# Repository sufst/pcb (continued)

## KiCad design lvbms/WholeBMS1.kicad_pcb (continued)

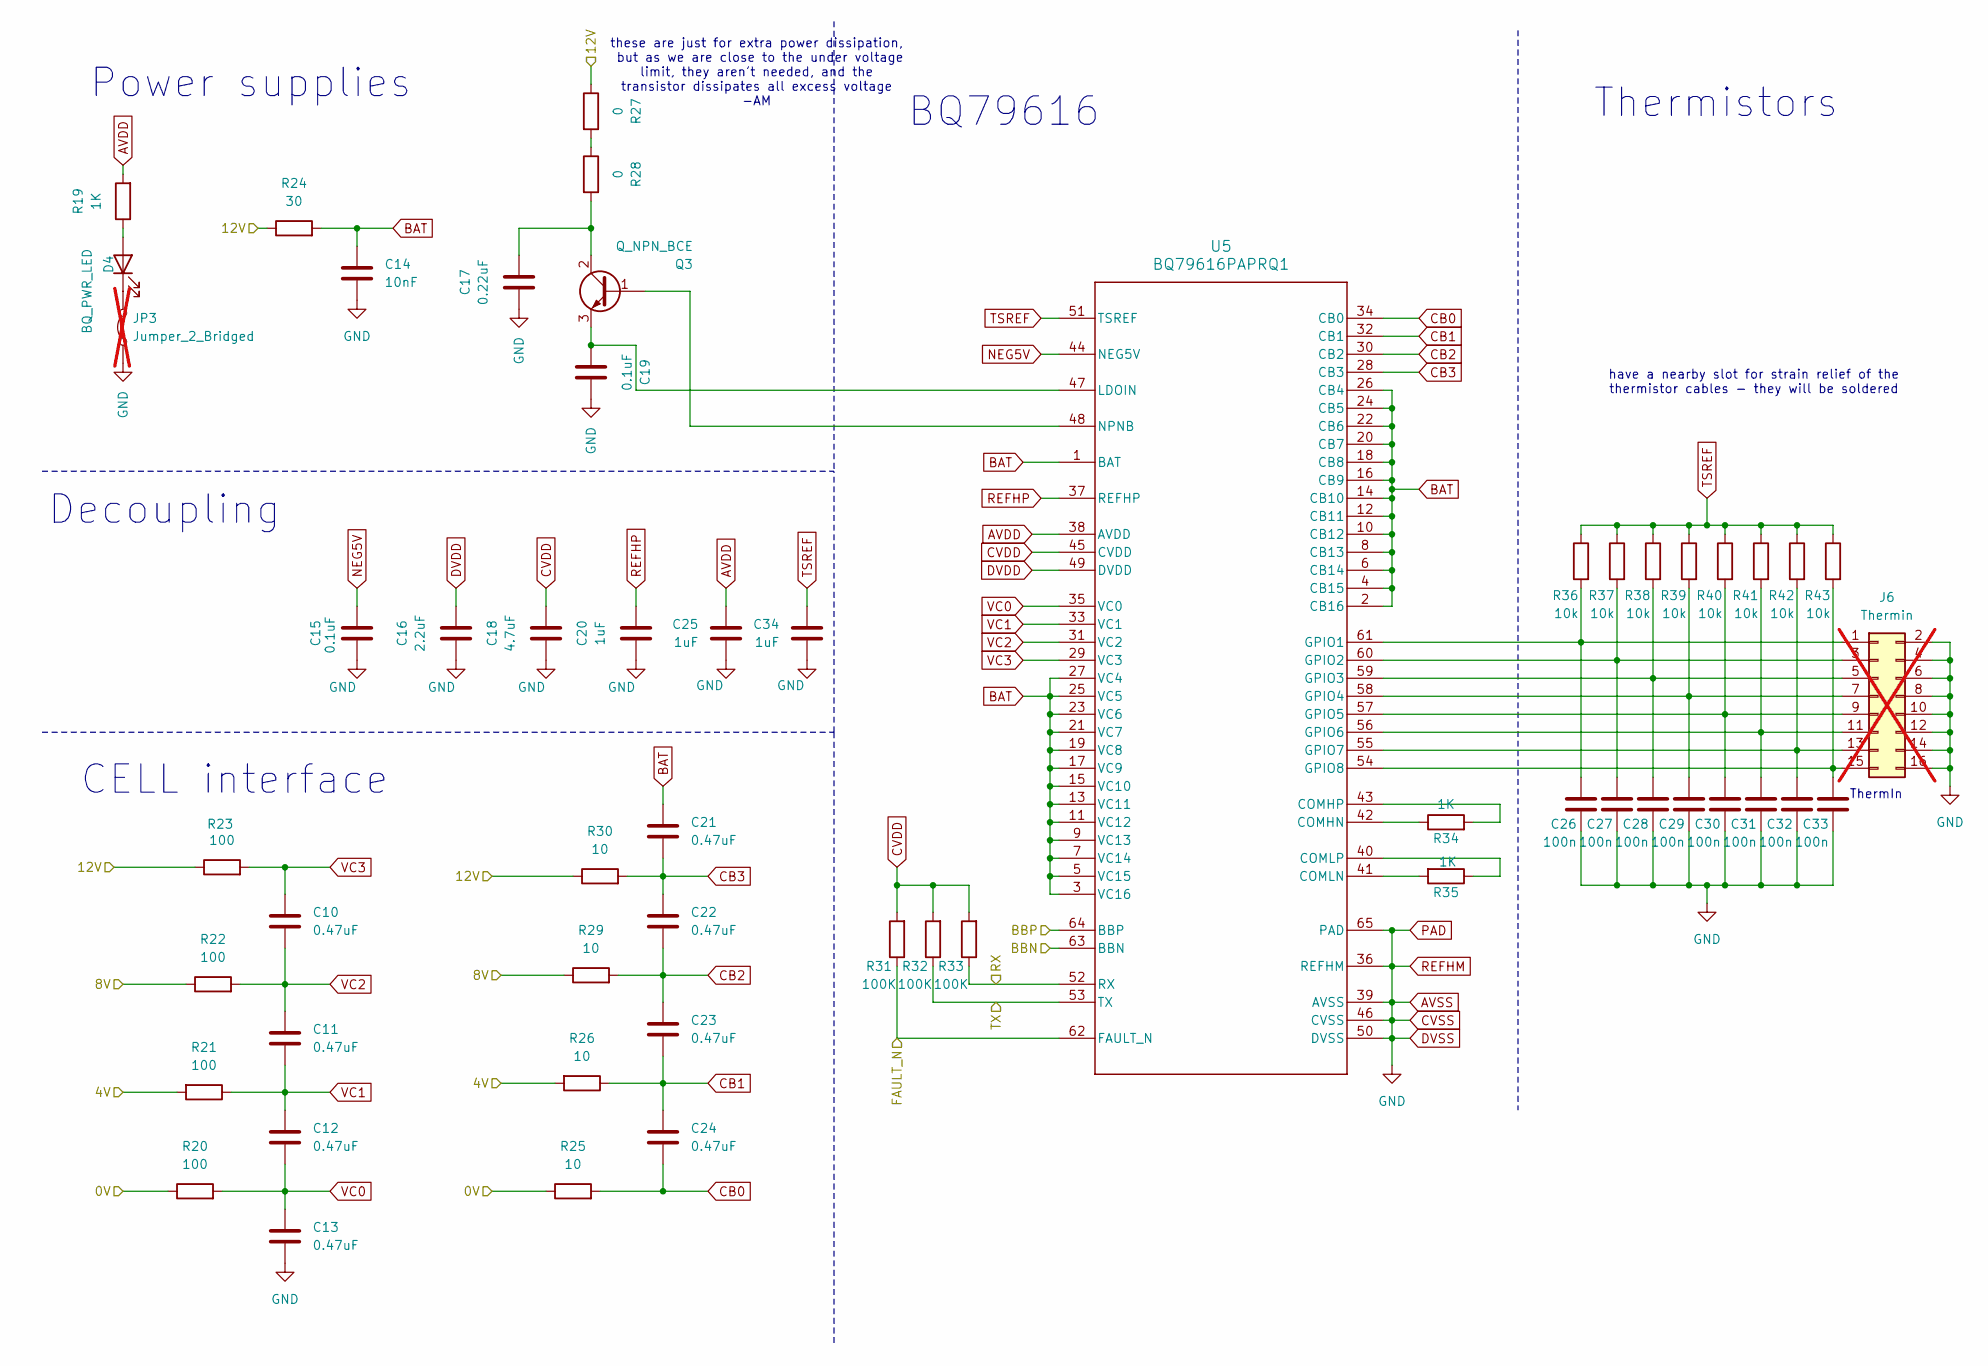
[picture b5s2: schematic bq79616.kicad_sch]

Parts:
C10, C11, C12, C13, C21, C22, C23, C24: 0.47uF; C_0603_1608Metric
C14: 10nF; C_0603_1608Metric
C15, C19: 0.1uF; C_0603_1608Metric
C16: 2.2uF; C_0603_1608Metric
C17: 0.22uF; C_0603_1608Metric
C18: 4.7uF; C_0603_1608Metric
C20, C25, C34: 1uF; C_0603_1608Metric
C26, C27, C28, C29, C30, C31, C32, C33: 100n; C_0603_1608Metric
D4: BQ_PWR_LED; LED_0805_2012Metric_Pad1.15x1.40mm_HandSolder
J6: Thermin; PinSocket_2x08_P2.54mm_Vertical; not fitted
JP3: Jumper_2_Bridged; SolderJumper-2_P1.3mm_Bridged_RoundedPad1.0x1.5mm; not fitted
Q3: Q_NPN_BCE; TO-252-3_TabPin2
R19, R34, R35: 1K; R_0603_1608Metric
R20, R21, R22, R23: 100; R_0603_1608Metric
R24: 30; R_0603_1608Metric
R25, R26, R29, R30: 10; R_2512_6332Metric
R27, R28: 0; R_0603_1608Metric
R31, R32, R33: 100K; R_0603_1608Metric
R36, R37, R38, R39, R40, R41, R42, R43: 10k; R_0603_1608Metric
U5: BQ79616PAPRQ1; PAP0064F-IPC_A

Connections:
/Bat1In: R21.2, R26.2; also elsewhere on the board
/Bat2In: R22.1, R29.1; also elsewhere on the board
/Bat3InFuse: U5.63 (BBN); also elsewhere on the board
/Bat3In_Sh: R23.1, R24.1, R27.1, R30.1, U5.64 (BBP); also elsewhere on the board
/FAULT_N: R31.1, U5.62 (FAULT_N); also elsewhere on the board
/MCU_RX: R32.1, U5.53 (TX); also elsewhere on the board
/MCU_TX: R33.1, U5.52 (RX); also elsewhere on the board
AVDD: C25.1, R19.2, U5.38 (AVDD)
AVSS: C13.2, C14.2, C15.2, C16.2, C17.1, C18.2, C19.1, C20.2, C25.2, C26.2, C27.2, C28.2, C29.2, C30.2, C31.2, C32.2, C33.2, C34.2, J6.2, J6.4, J6.6, J6.8, J6.10, J6.12, J6.14, J6.16, JP3.1 (A), R20.1, R25.1, U5.36 (REFHM), U5.39 (AVSS), U5.46 (CVSS), U5.50 (DVSS), U5.65 (PAD); also elsewhere on the board
BAT: C14.1, C21.1, R24.2, U5.1 (BAT), U5.2 (CB16), U5.3 (VC16), U5.4 (CB15), U5.5 (VC15), U5.6 (CB14), U5.7 (VC14), U5.8 (CB13), U5.9 (VC13), U5.10 (CB12), U5.11 (VC12), U5.12 (CB11), U5.13 (VC11), U5.14 (CB10), U5.15 (VC10), U5.16 (CB9), U5.17 (VC9), U5.18 (CB8), U5.19 (VC8), U5.20 (CB7), U5.21 (VC7), U5.22 (CB6), U5.23 (VC6), U5.24 (CB5), U5.25 (VC5), U5.26 (CB4), U5.27 (VC4)
CB0: C24.1, R25.2, U5.34 (CB0)
CB1: C23.2, C24.2, R26.1, U5.32 (CB1)
CB2: C22.2, C23.1, R29.2, U5.30 (CB2)
CB3: C21.2, C22.1, R30.2, U5.28 (CB3)
CVDD: C18.1, R31.2, R32.2, R33.2, U5.45 (CVDD)
DVDD: C16.1, U5.49 (DVDD)
NEG5V: C15.1, U5.44 (NEG5V)
unnamed: D4.2 (A), R19.1
unnamed: D4.1 (K), JP3.2 (B)
unnamed: C26.1, J6.1, R36.2, U5.61 (GPIO1)
unnamed: C27.1, J6.3, R37.2, U5.60 (GPIO2)
unnamed: C28.1, J6.5, R38.2, U5.59 (GPIO3)
unnamed: C29.1, J6.7, R39.2, U5.58 (GPIO4)
unnamed: C30.1, J6.9, R40.2, U5.57 (GPIO5)
unnamed: C31.1, J6.11, R41.2, U5.56 (GPIO6)
unnamed: C32.1, J6.13, R42.2, U5.55 (GPIO7)
unnamed: C33.1, J6.15, R43.2, U5.54 (GPIO8)
unnamed: Q3.1 (B), U5.48 (NPNB)
unnamed: C17.2, Q3.2 (C), R28.2
unnamed: C19.2, Q3.3 (E), U5.47 (LDOIN)
unnamed: R27.2, R28.1
unnamed: R34.1, U5.42 (COMHN)
unnamed: R34.2, U5.43 (COMHP)
unnamed: R35.2, U5.41 (COMLN)
unnamed: R35.1, U5.40 (COMLP)
REFHP: C20.1, U5.37 (REFHP)
TSREF: C34.1, R36.1, R37.1, R38.1, R39.1, R40.1, R41.1, R42.1, R43.1, U5.51 (TSREF)
VC0: C12.1, C13.1, R20.2, U5.35 (VC0)
VC1: C11.2, C12.2, R21.1, U5.33 (VC1)
VC2: C10.2, C11.1, R22.2, U5.31 (VC2)
VC3: C10.1, R23.2, U5.29 (VC3)

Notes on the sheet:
Thermistors
these are just for extra power dissipation, but as we are close to the under voltage limit, they aren't needed, and the transistor dissipates all excess voltage -AM
CELL interface
Power supplies
have a nearby slot for strain relief of the thermistor cables - they will be soldered
Decoupling
BQ79616
ThermIn

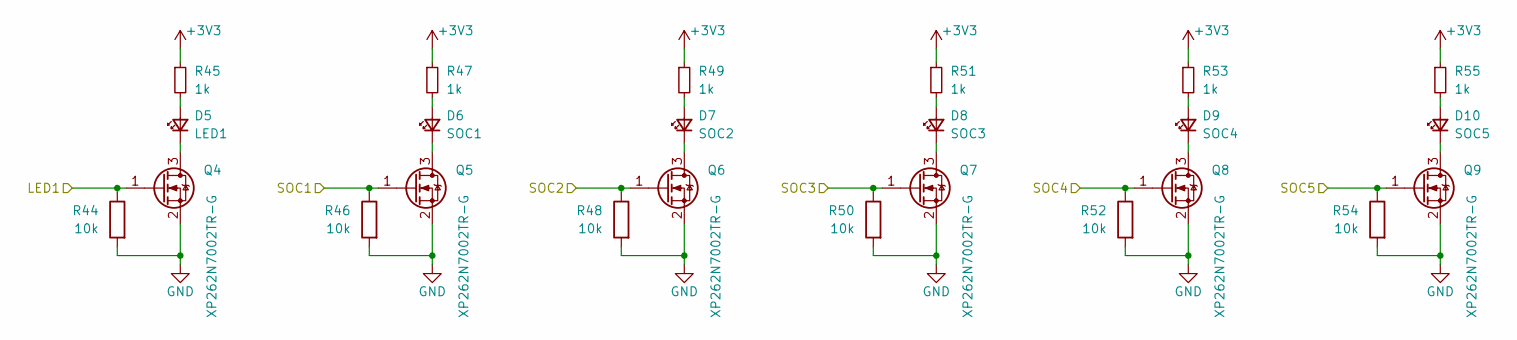
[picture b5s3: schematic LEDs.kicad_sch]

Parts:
D5: LED1; LED_0805_2012Metric_Pad1.15x1.40mm_HandSolder
D6: SOC1; LED_0805_2012Metric_Pad1.15x1.40mm_HandSolder
D7: SOC2; LED_0805_2012Metric_Pad1.15x1.40mm_HandSolder
D8: SOC3; LED_0805_2012Metric_Pad1.15x1.40mm_HandSolder
D9: SOC4; LED_0805_2012Metric_Pad1.15x1.40mm_HandSolder
D10: SOC5; LED_0805_2012Metric_Pad1.15x1.40mm_HandSolder
Q4, Q5, Q6, Q7, Q8, Q9: XP262N7002TR-G; SOT-23
R44, R46, R48, R50, R52, R54: 10k; R_0603_1608Metric
R45, R47, R49, R51, R53, R55: 1k; R_0603_1608Metric

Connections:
+3V3: R45.1, R47.1, R49.1, R51.1, R53.1, R55.1; also elsewhere on the board
/LED1: Q4.1 (G), R44.1; also elsewhere on the board
/SOC1: Q5.1 (G), R46.1; also elsewhere on the board
/SOC2: Q6.1 (G), R48.1; also elsewhere on the board
/SOC3: Q7.1 (G), R50.1; also elsewhere on the board
/SOC4: Q8.1 (G), R52.1; also elsewhere on the board
/SOC5: Q9.1 (G), R54.1; also elsewhere on the board
AVSS: Q4.2 (S), Q5.2 (S), Q6.2 (S), Q7.2 (S), Q8.2 (S), Q9.2 (S), R44.2, R46.2, R48.2, R50.2, R52.2, R54.2; also elsewhere on the board
unnamed: D5.2 (A), R45.2
unnamed: D5.1 (K), Q4.3 (D)
unnamed: D6.2 (A), R47.2
unnamed: D6.1 (K), Q5.3 (D)
unnamed: D7.2 (A), R49.2
unnamed: D7.1 (K), Q6.3 (D)
unnamed: D8.2 (A), R51.2
unnamed: D8.1 (K), Q7.3 (D)
unnamed: D9.2 (A), R53.2
unnamed: D9.1 (K), Q8.3 (D)
unnamed: D10.2 (A), R55.2
unnamed: D10.1 (K), Q9.3 (D)

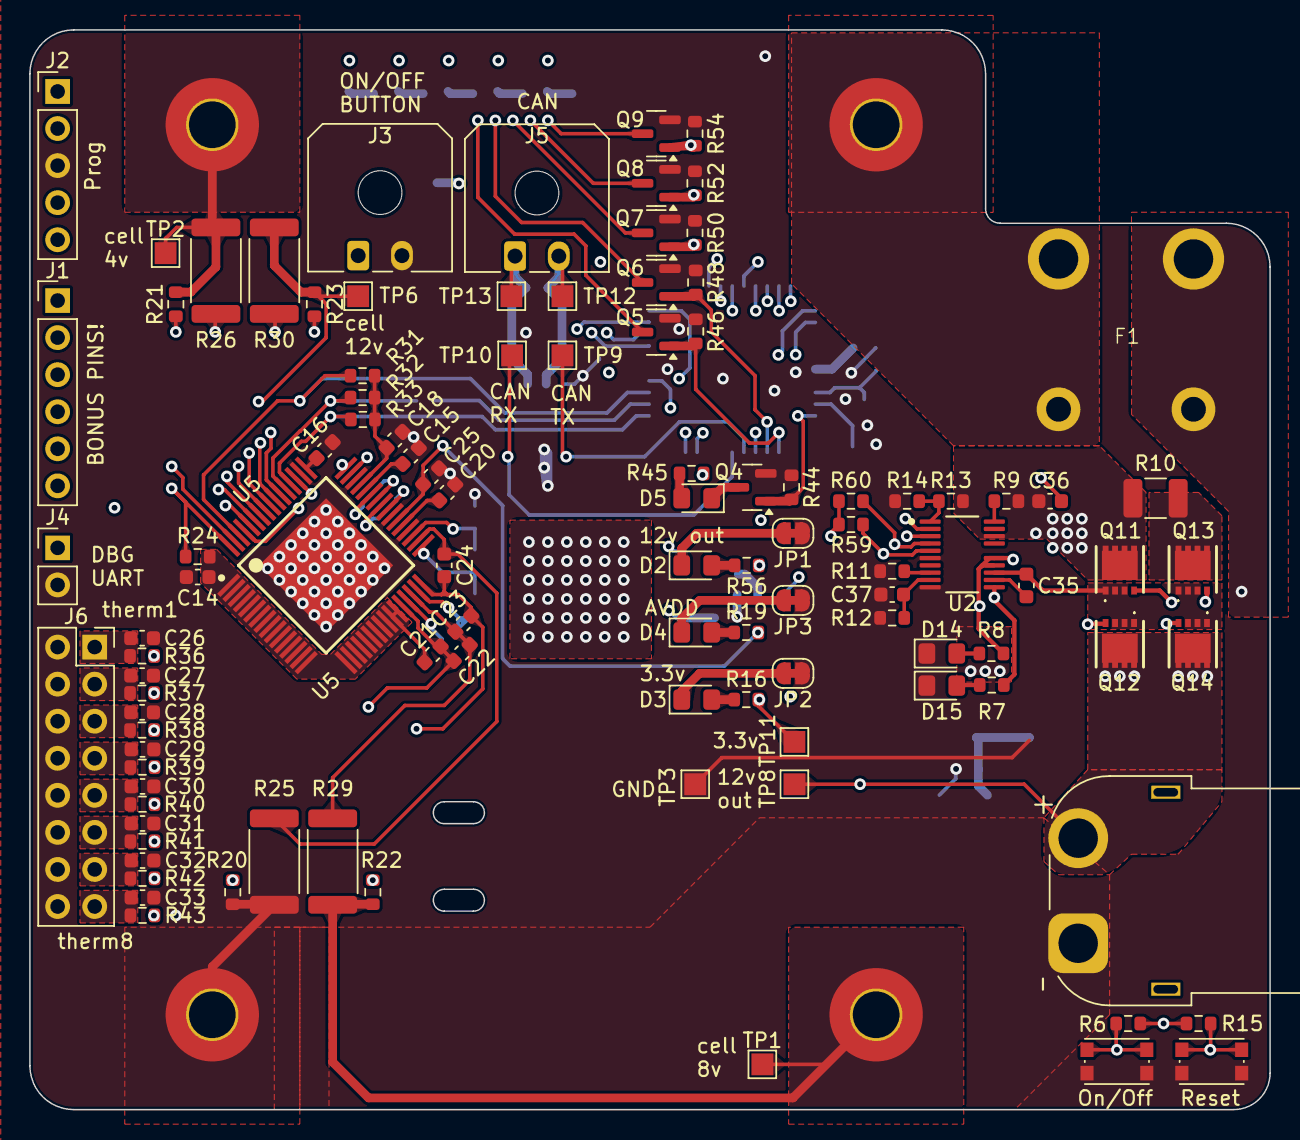
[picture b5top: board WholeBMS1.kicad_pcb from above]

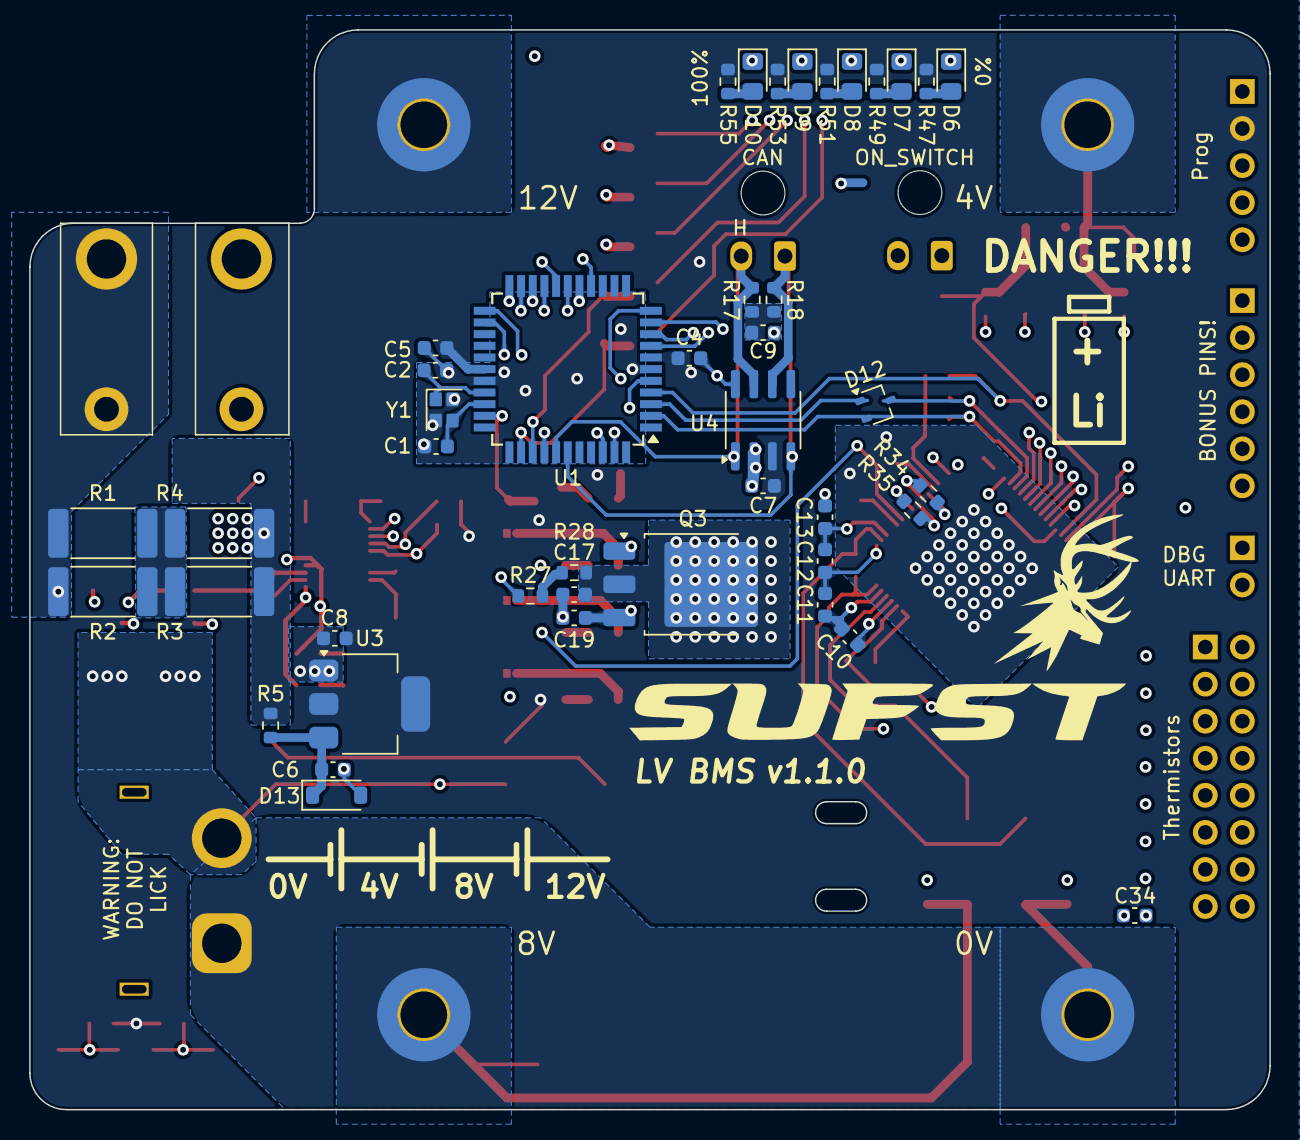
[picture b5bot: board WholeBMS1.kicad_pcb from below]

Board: 6 copper layers, 85.0 x 74.0 mm, 151 parts (44 on the bottom side), 102 nets.

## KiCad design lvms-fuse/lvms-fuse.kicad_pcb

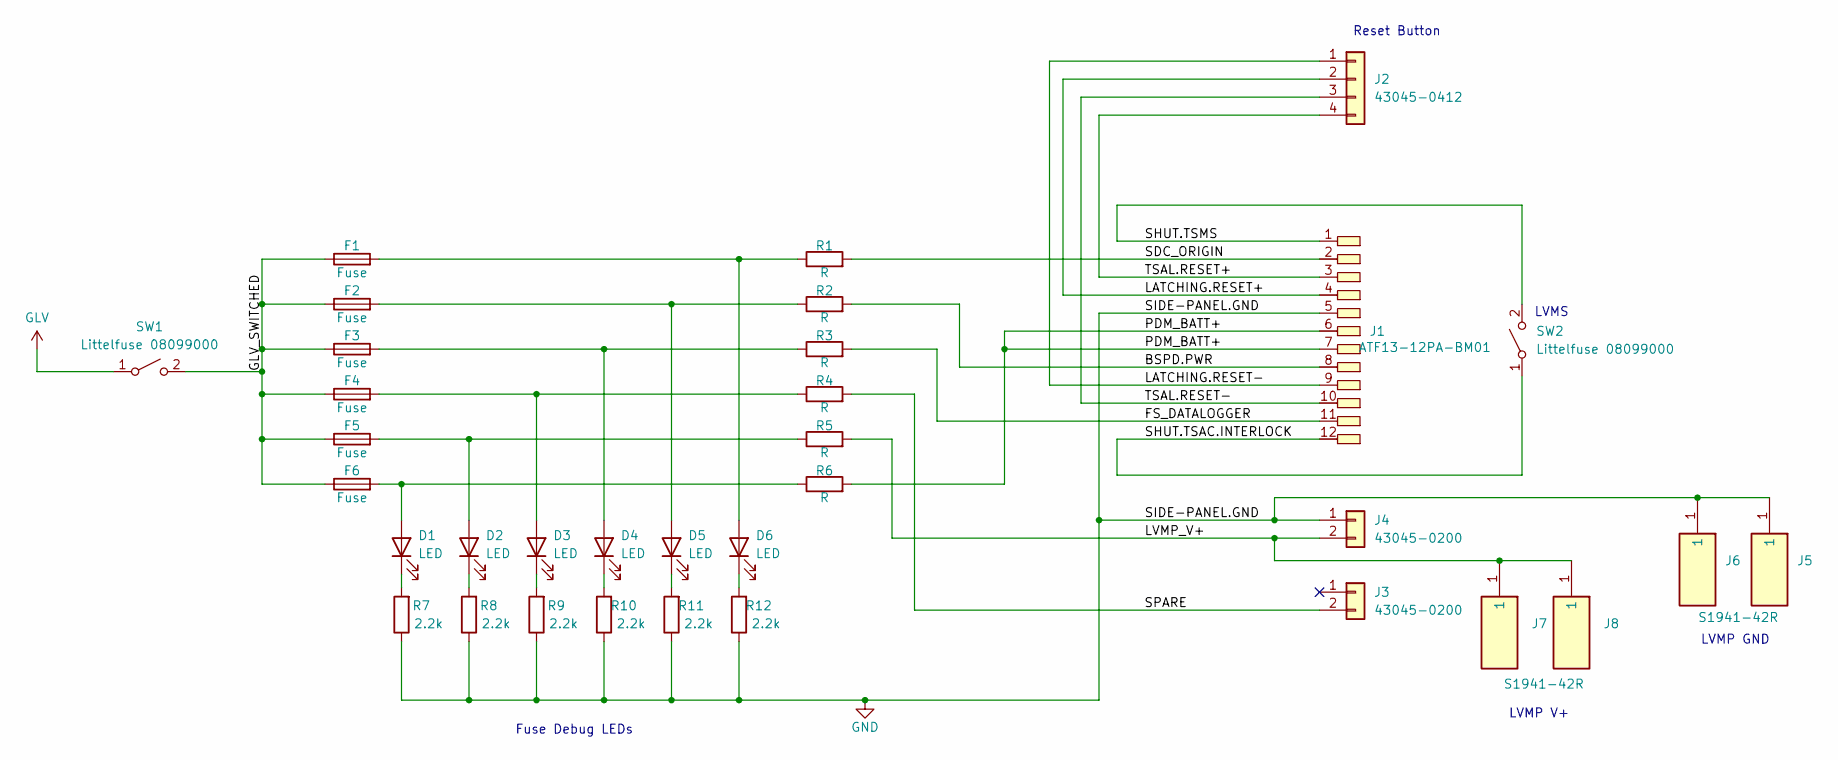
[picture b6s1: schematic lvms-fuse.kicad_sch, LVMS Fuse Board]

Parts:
D1, D2, D3, D4, D5, D6: LED; LED_0603_1608Metric
F1, F2, F3, F4, F5, F6: Fuse; 01000066Z
J1: ATF13-12PA-BM01; ATF1312PABM01
J2: 43045-0412; Molex_Micro-Fit_3.0_43045-0412_2x02_P3.00mm_Vertical
J3, J4: 43045-0200; Molex_Micro-Fit_3.0_43045-0200_2x01_P3.00mm_Horizontal
J5, J6, J7, J8: S1941-42R; S194142R_THT_secured; Mouser Part Number 855-S1941-42R
R1, R2, R3, R4, R5, R6: R; R_2512_6332Metric
R7, R8, R9, R10, R11, R12: 2.2k; R_0603_1608Metric
SW1, SW2: Littelfuse 08099000

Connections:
/BSPD.PWR: J1.8, R2.2
/FS_DATALOGGER: J1.11, R3.2
/GLV_SWITCHED: F1.1, F2.1, F3.1, F4.1, F5.1, F6.1, SW1.2 (B)
/LATCHING.RESET+: J1.4, J2.2
/LATCHING.RESET-: J1.9, J2.1
/LVMP_V+: J4.2, J7.1, J8.1, R5.2
/PDM_BATT+: J1.6, J1.7, R6.2
/SDC_ORIGIN: J1.2, R1.2
/SHUT.TSAC.INTERLOCK: J1.12, SW2.1 (A)
/SHUT.TSMS: J1.1, SW2.2 (B)
/SIDE-PANEL.GND: J1.5, J4.1, J5.1, J6.1, R7.1, R8.1, R9.1, R10.1, R11.1, R12.1
/SPARE: J3.2, R4.2
/TSAL.RESET+: J1.3, J2.4
/TSAL.RESET-: J1.10, J2.3
GLV: SW1.1 (A)
unnamed: D1.2 (A), F6.2, R6.1
unnamed: D1.1 (K), R7.2
unnamed: D2.2 (A), F5.2, R5.1
unnamed: D2.1 (K), R8.2
unnamed: D3.2 (A), F4.2, R4.1
unnamed: D3.1 (K), R9.2
unnamed: D4.2 (A), F3.2, R3.1
unnamed: D4.1 (K), R10.2
unnamed: D5.2 (A), F2.2, R2.1
unnamed: D5.1 (K), R11.2
unnamed: D6.2 (A), F1.2, R1.1
unnamed: D6.1 (K), R12.2

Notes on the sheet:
Fuse Debug LEDs
LVMP GND
LVMS
Reset Button
LVMP V+

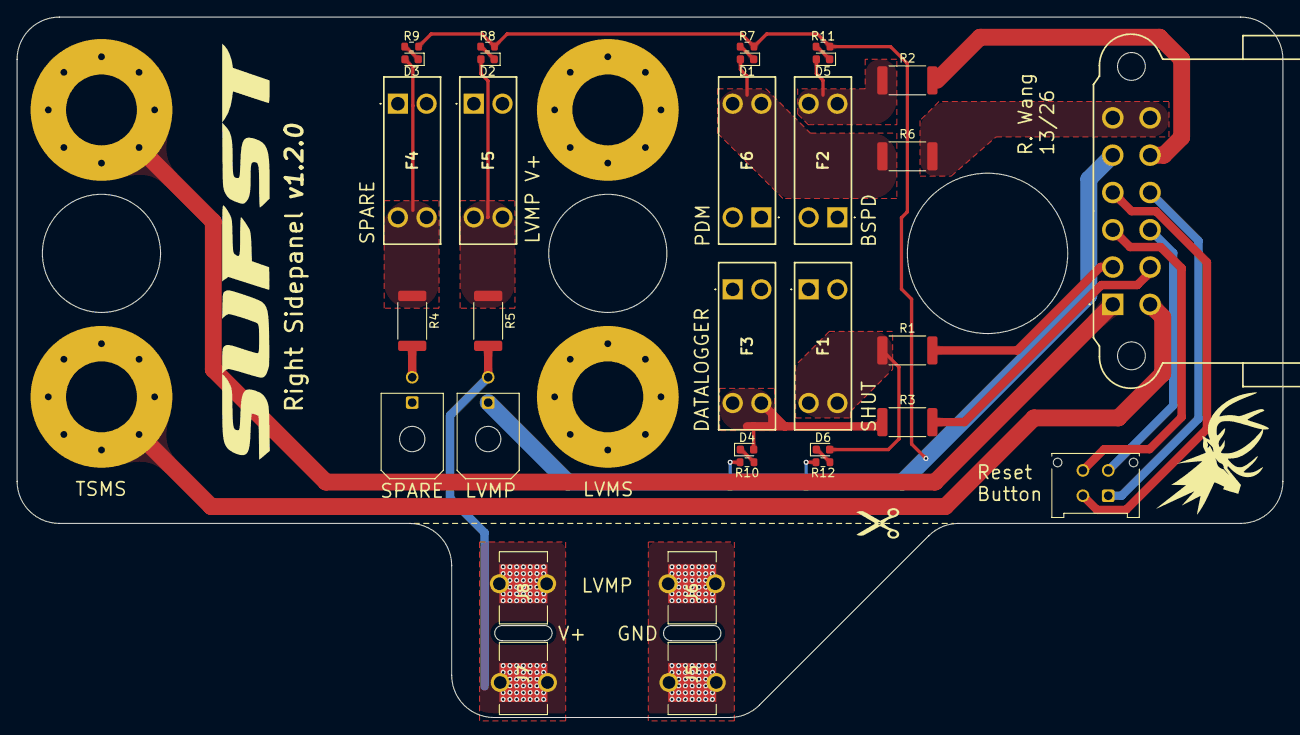
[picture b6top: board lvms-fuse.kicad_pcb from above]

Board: 2 copper layers, 150.0 x 83.0 mm, 34 parts (0 on the bottom side), 26 nets.

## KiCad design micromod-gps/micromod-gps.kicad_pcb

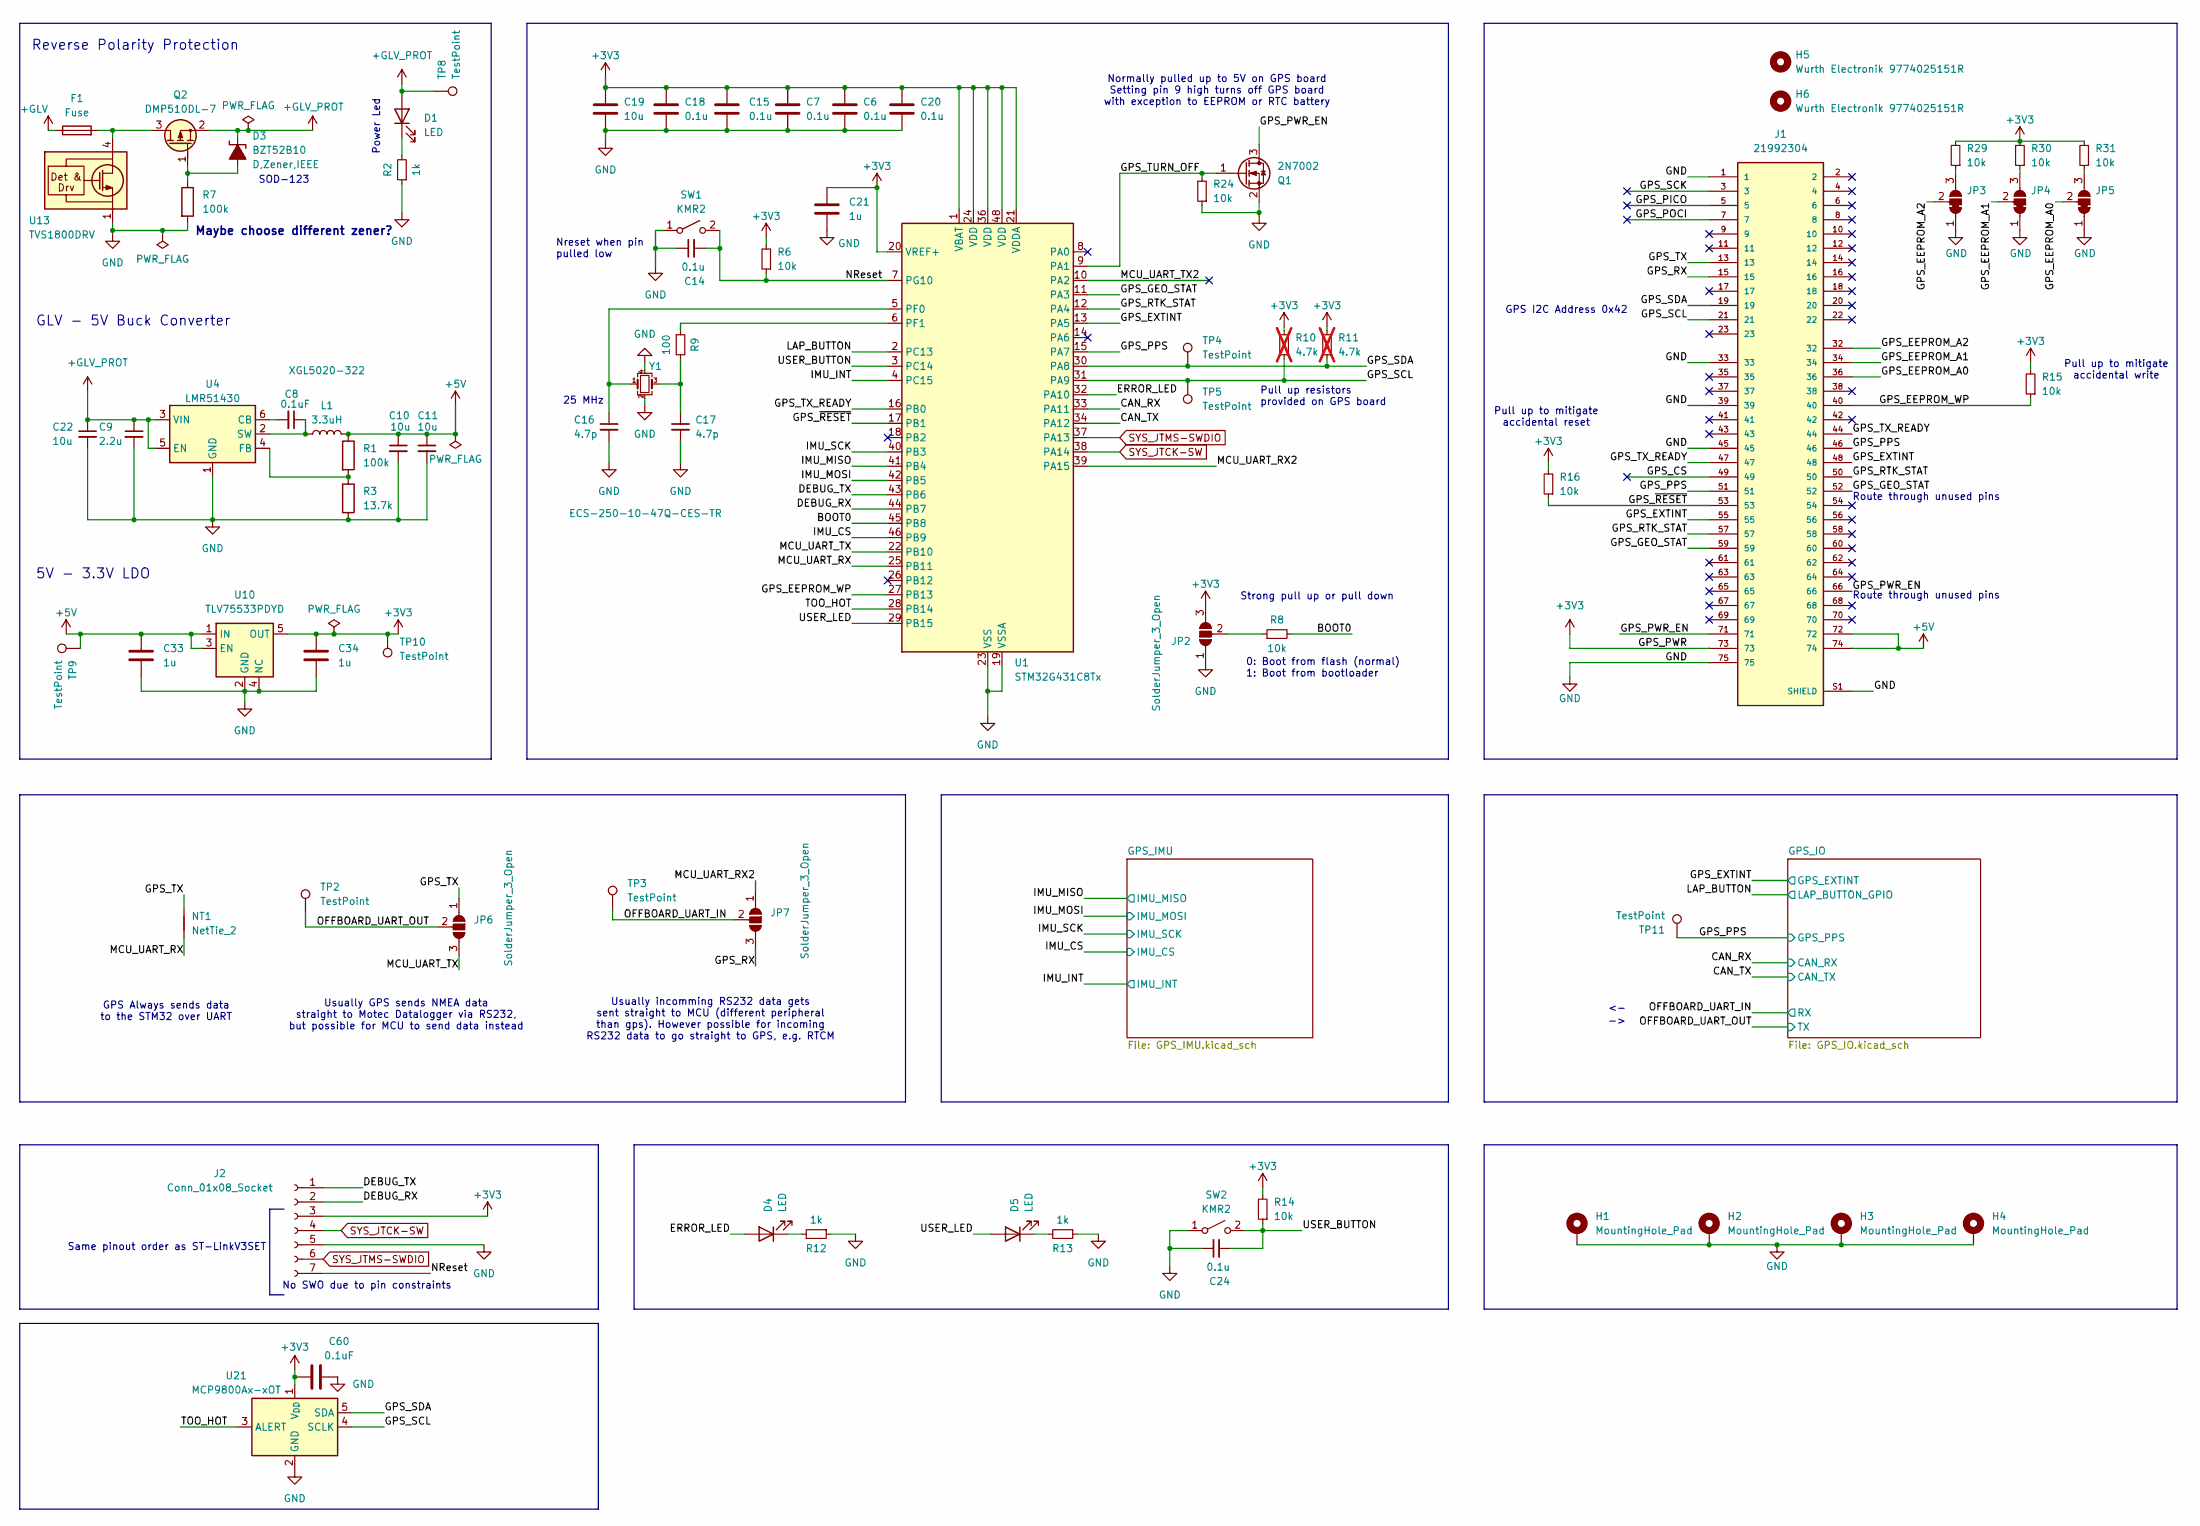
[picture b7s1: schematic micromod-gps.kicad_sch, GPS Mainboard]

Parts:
C6, C7, C14, C15, C18, C20, C24: 0.1u; C_0603_1608Metric_Pad1.08x0.95mm_HandSolder; MPN CL10B104KB85PNL
C8: 0.1uF; C_0603_1608Metric_Pad1.08x0.95mm_HandSolder; MPN CL10B104KB85PNL
C9: 2.2u; C_0603_1608Metric_Pad1.08x0.95mm_HandSolder; MPN TMK107ABJ225KA-T
C10, C11: 10u; C_0805_2012Metric_Pad1.18x1.45mm_HandSolder; MPN CL10A106MA8NRWC
C16, C17: 4.7p; C_0603_1608Metric_Pad1.08x0.95mm_HandSolder; MPN 0402N4R7C500CT
C19, C22: 10u; C_0603_1608Metric_Pad1.08x0.95mm_HandSolder; MPN CL10A106MA8NRWC
C21, C33, C34: 1u; C_0603_1608Metric_Pad1.08x0.95mm_HandSolder; MPN UMK107BJ105KA-T
C60: 0.1uF; C_0603_1608Metric_Pad1.08x0.95mm_HandSolder; MPN CL10B104KB85PNL; Mouser Order Number 81-GRM155R62A104KE4J
D1, D4, D5: LED; LED_0603_1608Metric_Pad1.05x0.95mm_HandSolder
D3: BZT52B10; D_SOD-123; MPN BZT52B10
F1: Fuse; Fuse_0603_1608Metric_Pad1.05x0.95mm_HandSolder
H1, H2, H3, H4: MountingHole_Pad; MountingHole_3.2mm_M3_Pad_Via
H5, H6: Wurth Electronik 9774025151R; 9774025151R; MPN 9774025151R
J1: 21992304; TE_21992304; MPN 21992304
J2: Conn_01x08_Socket; PinSocket_1x07_P2.54mm_Vertical
JP2, JP6, JP7: SolderJumper_3_Open; SolderJumper-3_P1.3mm_Open_RoundedPad1.0x1.5mm
JP3, JP4, JP5: SolderJumper_3_Bridged12; SolderJumper-3_P1.3mm_Bridged12_RoundedPad1.0x1.5mm
L1: 3.3uH; L_Coilcraft_XAL5020-XXX; MPN XGL5020-322
NT1: NetTie_2; NetTie-2_SMD_Pad0.5mm
Q1: 2N7002; SOT-23; MPN XP262N7002TR-G
Q2: DMP510DL-7; SOT-23; MPN DMP510DL
R1, R7: 100k; R_0603_1608Metric_Pad0.98x0.95mm_HandSolder; MPN RT0603FRE10100KL
R2, R12, R13: 1k; R_0603_1608Metric_Pad0.98x0.95mm_HandSolder; MPN RNCP0603FTD1K00
R3: 13.7k; R_0603_1608Metric_Pad0.98x0.95mm_HandSolder; MPN RT0603FRE0713K7L
R6, R8, R14, R15, R16, R24, R29, R30, R31: 10k; R_0603_1608Metric_Pad0.98x0.95mm_HandSolder; MPN RT0603RF1310KL
R9: 100; R_0603_1608Metric_Pad0.98x0.95mm_HandSolder; MPN RT0603FRE07100RL
R10, R11: 4.7k; R_0603_1608Metric_Pad0.98x0.95mm_HandSolder; MPN RC0603FR-074K7P; not fitted
SW1, SW2: KMR2; SW_Push_1P1T_NO_CK_KMR2; MPN KMR221NG LFS
TP2, TP3, TP4, TP5, TP8, TP9, TP10, TP11: TestPoint; Keystone 5015; MPN 5015
U1: STM32G431C8Tx; LQFP-48_7x7mm_P0.5mm; MPN STM32G431C8Tx
U4: LMR51430; SOT-23-6; MPN LMR51430YDDCR
U10: TLV75533PDYD
U13: TVS1800DRV; WSON-6-1EP_2x2mm_P0.65mm_EP1x1.6mm
U21: MCP9800Ax-xOT; SOT-23-5; MPN MCP9800A5T-M/OT; Mouser Order Number 579-MCP9800A5T-M/OT
Y1: ECS-250-10-47Q-CES-TR; Resonator_SMD_ECS_ECX-1247Q_1.6x1.2x0.3mm; MPN ECS-250-10-47Q-CES-TR

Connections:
+3V3: C6.1, C7.1, C15.1, C18.1, C19.1, C20.1, C21.1, C34.1, C60.1, J1.73, J2.3, JP2.3 (B), R6.2, R10.2, R11.2, R14.2, R15.2, R16.2, R29.2, R30.2, R31.2, TP10.1, U1.1 (VBAT), U1.20 (VREF+), U1.21 (VDDA), U1.24 (VDD), U1.36 (VDD), U1.48 (VDD), U10.5 (OUT), U21.1 (V_{DD}); also elsewhere on the board
+5V: C10.1, C11.1, C33.1, J1.72, J1.74, L1.2, R1.1, TP9.1, U10.1 (IN), U10.3 (EN)
+GLV: F1.1; also elsewhere on the board
+GLV_PROT: C9.1, C22.1, D1.2 (A), D3.1 (K-), Q2.2 (S), TP8.1, U4.3 (VIN), U4.5 (EN); also elsewhere on the board
/BOOT0: R8.2, U1.45 (PB8)
/CAN_RX: U1.33 (PA11); also elsewhere on the board
/CAN_TX: U1.34 (PA12); also elsewhere on the board
/DEBUG_RX: J2.2, U1.44 (PB7)
/DEBUG_TX: J2.1, U1.43 (PB6)
/ERROR_LED: D4.2 (A), U1.32 (PA10)
/GPS_CS: J1.49
/GPS_EEPROM_A0: J1.36, JP5.2 (C)
/GPS_EEPROM_A1: J1.34, JP4.2 (C)
/GPS_EEPROM_A2: J1.32, JP3.2 (C)
/GPS_EEPROM_WP: J1.40, R15.1, U1.27 (PB13)
/GPS_EXTINT: J1.48, J1.55, U1.13 (PA5); also elsewhere on the board
/GPS_GEO_STAT: J1.52, J1.59, U1.11 (PA3)
/GPS_PICO: J1.5
/GPS_POCI: J1.7
/GPS_PPS: J1.46, J1.51, TP11.1, U1.15 (PA7); also elsewhere on the board
/GPS_PWR_EN: J1.66, J1.71, Q1.3 (D)
/GPS_RTK_STAT: J1.50, J1.57, U1.12 (PA4)
/GPS_RX: J1.15, JP7.3 (B)
/GPS_SCK: J1.3
/GPS_SCL: J1.21, R10.1, TP5.1, U1.31 (PA9), U21.4 (SCLK)
/GPS_SDA: J1.19, R11.1, TP4.1, U1.30 (PA8), U21.5 (SDA)
/GPS_TURN_OFF: Q1.1 (G), R24.2, U1.9 (PA1)
/GPS_TX: J1.13, JP6.1 (A), NT1.2
/GPS_TX_READY: J1.44, J1.47, U1.16 (PB0)
/GPS_~RESET: J1.53, R16.1, U1.17 (PB1)
/IMU_CS: U1.46 (PB9); also elsewhere on the board
/IMU_INT: U1.4 (PC15); also elsewhere on the board
/IMU_MISO: U1.41 (PB4); also elsewhere on the board
/IMU_MOSI: U1.42 (PB5); also elsewhere on the board
/IMU_SCK: U1.40 (PB3); also elsewhere on the board
/LAP_BUTTON: U1.2 (PC13); also elsewhere on the board
/MCU_UART_RX: NT1.1, U1.25 (PB11)
/MCU_UART_RX2: JP7.1 (A), U1.39 (PA15)
/MCU_UART_TX: JP6.3 (B), U1.22 (PB10)
/MCU_UART_TX2: U1.10 (PA2)
/NReset: C14.2, J2.7, R6.1, SW1.2 (B), U1.7 (PG10)
/OFFBOARD_UART_IN: JP7.2 (C), TP3.1; also elsewhere on the board
/OFFBOARD_UART_OUT: JP6.2 (C), TP2.1; also elsewhere on the board
/TOO_HOT: U1.28 (PB14), U21.3 (ALERT)
/USER_BUTTON: C24.2, R14.1, SW2.2 (B), U1.3 (PC14)
/USER_LED: D5.2 (A), U1.29 (PB15)
GND: C6.2, C7.2, C9.2, C10.2, C11.2, C14.1, C15.2, C16.2, C17.2, C18.2, C19.2, C20.2, C21.2, C22.2, C24.1, C33.2, C34.2, C60.2, H1.1, H2.1, H3.1, H4.1, J1.1, J1.33, J1.39, J1.45, J1.75, J1.S1 (SHIELD), J1.S2 (SHIELD), J2.5, JP2.1 (A), JP3.1 (A), JP4.1 (A), JP5.1 (A), Q1.2 (S), R2.1, R3.2, R7.2, R12.1, R13.1, R24.1, SW1.1 (A), SW2.1 (A), U1.19 (VSSA), U1.23 (VSS), U1.35 (VSS), U1.47 (VSS), U4.1 (GND), U10.2 (GND), U10.4 (NC), U10.6 (GND), U13.1 (GND), U13.2 (GND), U13.3 (GND), U13.7 (GND), U21.2 (GND), Y1.2, Y1.4; also elsewhere on the board
unnamed: C17.1, R9.2, Y1.3
unnamed: D1.1 (K), R2.2
unnamed: D3.2 (A+), Q2.1 (G), R7.1
unnamed: D4.1 (K), R12.2
unnamed: D5.1 (K), R13.2
unnamed: JP2.2 (C), R8.1
unnamed: JP3.3 (B), R29.1
unnamed: JP4.3 (B), R30.1
unnamed: JP5.3 (B), R31.1
unnamed: F1.2, Q2.3 (D), U13.4 (IN), U13.5 (IN), U13.6 (IN)
unnamed: C16.1, U1.5 (PF0), Y1.1
unnamed: R9.1, U1.6 (PF1)
unnamed: C8.2, U4.6 (CB)
unnamed: R1.2, R3.1, U4.4 (FB)
unnamed: C8.1, L1.1, U4.2 (SW)
SYS_JTCK-SW: J2.4, U1.38 (PA14)
SYS_JTMS-SWDIO: J2.6, U1.37 (PA13)

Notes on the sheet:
Route through unused pins
Strong pull up or pull down
Pull up resistors provided on GPS board
25 MHz
Nreset when pin pulled low
0: Boot from flash (normal) 1: Boot from bootloader
Power Led
Same pinout order as ST-LinkV3SET
No SWO due to pin constraints
Usually incomming RS232 data gets sent straight to MCU (different peripheral than gps). However possible for incoming RS232 data to go straight to GPS, e.g. RTCM
Usually GPS sends NMEA data straight to Motec Datalogger via RS232, but possible for MCU to send data instead
Normally pulled up to 5V on GPS board Setting pin 9 high turns off GPS board with exception to EEPROM or RTC battery
SOD-123
5V - 3.3V LDO
GPS Always sends data to the STM32 over UART
Maybe choose different zener?
GLV - 5V Buck Converter
Pull up to mitigate accidental reset
Reverse Polarity Protection
Pull up to mitigate accidental write
GPS I2C Address 0x42

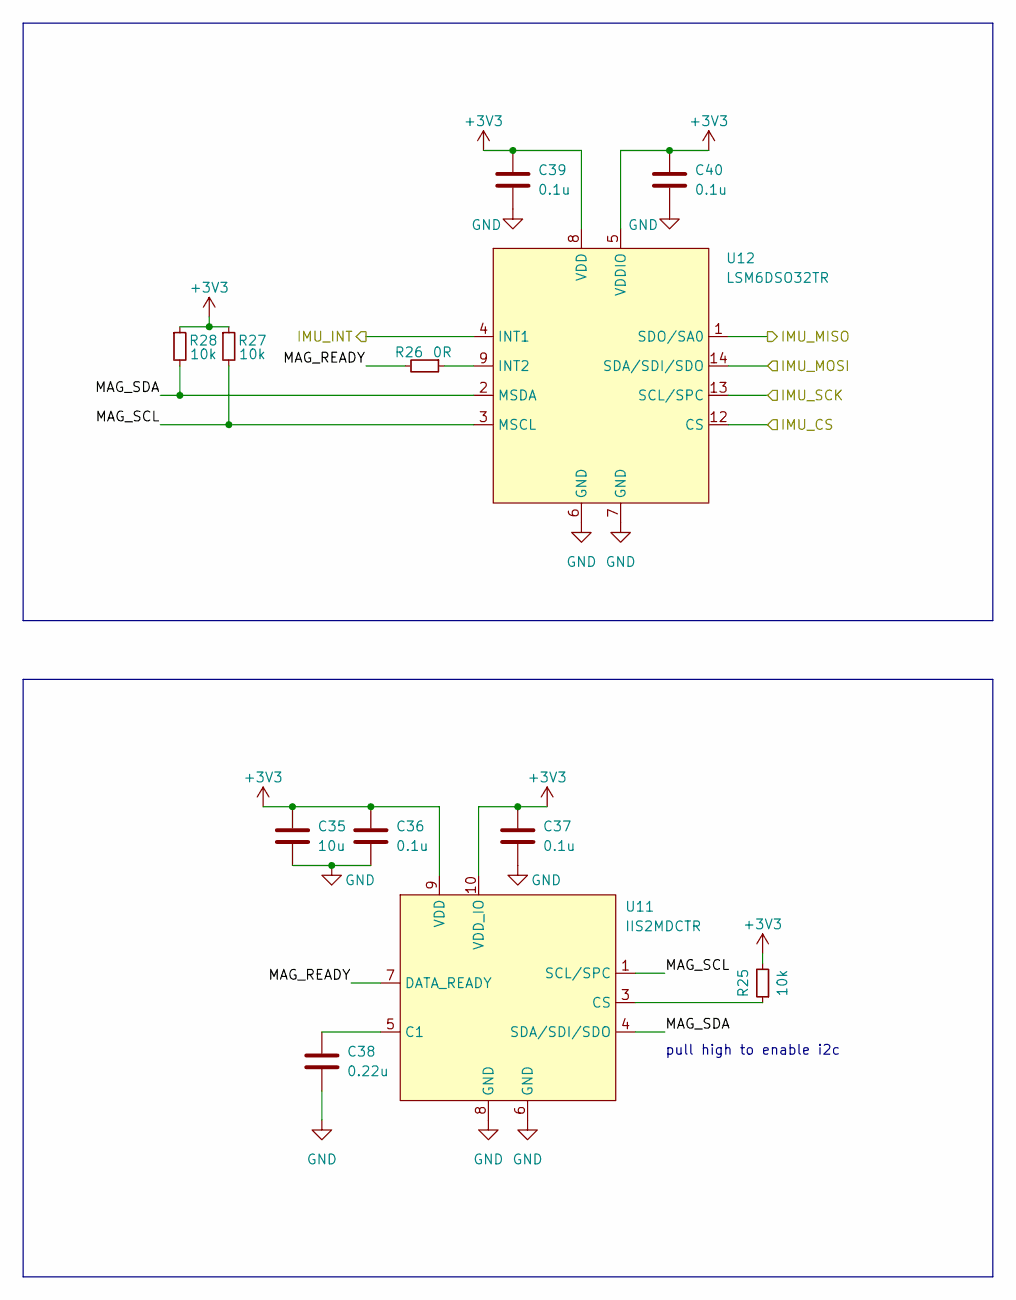
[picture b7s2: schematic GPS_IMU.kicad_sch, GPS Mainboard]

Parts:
C35: 10u; C_0603_1608Metric_Pad1.08x0.95mm_HandSolder; MPN CL10A106MA8NRWC
C36, C37, C39, C40: 0.1u; C_0603_1608Metric_Pad1.08x0.95mm_HandSolder; MPN CL10B104KB85PNL
C38: 0.22u; C_0603_1608Metric_Pad1.08x0.95mm_HandSolder; MPN 0603B224K500CT
R25, R27, R28: 10k; R_0603_1608Metric_Pad0.98x0.95mm_HandSolder; MPN RT0603RF1310KL
R26: 0R; R_0603_1608Metric_Pad0.98x0.95mm_HandSolder; MPN RC0603FR-100RL
U11: IIS2MDCTR; LGA-12_2x2mm_P0.5mm; MPN IIS2MDCTR
U12: LSM6DSO32TR; LGA-14_3x2.5mm_P0.5mm_LayoutBorder3x4y; MPN LSM6DSO32TR

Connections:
+3V3: C35.1, C36.1, C37.1, C39.1, C40.1, R25.2, R27.1, R28.1, U11.9 (VDD), U11.10 (VDD_IO), U12.5 (VDDIO), U12.8 (VDD); also elsewhere on the board
/GPS_IMU/MAG_READY: R26.2, U11.7 (DATA_READY)
/GPS_IMU/MAG_SCL: R27.2, U11.1 (SCL/SPC), U12.3 (MSCL)
/GPS_IMU/MAG_SDA: R28.2, U11.4 (SDA/SDI/SDO), U12.2 (MSDA)
/IMU_CS: U12.12 (CS); also elsewhere on the board
/IMU_INT: U12.4 (INT1); also elsewhere on the board
/IMU_MISO: U12.1 (SDO/SA0); also elsewhere on the board
/IMU_MOSI: U12.14 (SDA/SDI/SDO); also elsewhere on the board
/IMU_SCK: U12.13 (SCL/SPC); also elsewhere on the board
GND: C35.2, C36.2, C37.2, C38.2, C39.2, C40.2, U11.6 (GND), U11.8 (GND), U12.6 (GND), U12.7 (GND); also elsewhere on the board
unnamed: C38.1, U11.5 (C1)
unnamed: R25.1, U11.3 (CS)
unnamed: R26.1, U12.9 (INT2)

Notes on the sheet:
pull high to enable i2c
